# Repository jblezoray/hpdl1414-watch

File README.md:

# HPDL-1414 Watch

A minimalist watch built around an [HPDL-1414](https://www.datasheetarchive.com/HPDL-1414-datasheet.html) 4-character alphanumeric display, driven by an ATmega32 microcontroller.

If you're brave enougth, you'll find anything you need to build it yourself in this repo.

There is a demo of the watch on youtube:

## Hardware

| Component | Details                                 |
| --------- | --------------------------------------- |
| MCU       | atmega328p                              |
| Display   | HPDL-1414 (4 × 16-segment alphanumeric) |
| RTC       | DS3231 (I2C)                            |
| Storage   | EEPROM (SPI)                            |
| Input     | 2 buttons                               |

You'll also need:

- A 3D printer for the case,
- A provider for the HPDL1414 displays. Aliexpress is a good source.
- I ordered the pcbs from jlcpcb. I chose to solder everything myself, but I think it'd be more reasonnable to order with all the components already soldered, except the display as they don't list it.

## Features

- Time display with configurable transitions
- Adjustable luminosity (stored in EEPROM)
- Low-power screen-off state
- State machine architecture

## Project Structure

```
hpdl-1414.ino          # Main sketch
src/
  screen-hpdl1414/     # HPDL-1414 driver
  rtc-ds3231/          # DS3231 RTC driver
  button/              # Button handler
  blinker/             # LED blinker
  persist-configuration/ # EEPROM persistence
  vcc-controller/      # Power control
  states/              # State machine
  pins.h               # Pin definitions
3dmodels/              # Model for the 3D printed case
```

## Watch PCB schematics

Open the schematics (`pcb/hpdl1414/hpdl1414.kicad_sch` and `pcb/hpdl1414/hpdl1414.kicad_pcb`) with [kicad 9.0.1](https://www.kicad.org/).

Here is the first prototype of the PCB I made. It offers a full view of all the components on one side:

And here is the final one that is in the watch. It is much smaller:

## Watch case

Open ‘3dmodels/HPDL1414-watch-round.FCStd‘ with [FreeCAD 1.0.2](https://www.freecad.org/). Export it part by part, and print it with your favorite 3d printer. I have great results with a [Bambu lab A1 mini](https://bambulab.com/en-eu/a1-mini).

You'll have to use threaded inserts, and M1.5 screws to bolt the back of the case:

## Watch software

I used a Mac for developping this project, but it should work with little to no adjustement on linux. Sorry Windows users, you're on your own on this one.

Also, I find the Arduino IDE really bad, but their libs are ok. So only their CLI is needed. Once installed, everything can be handled by the Makefile.

### Prerequisites

- [Arduino CLI](https://arduino.github.io/arduino-cli/latest/installation/)
- An Arduino board used as ISP programmer (e.g. Uno)

```bash
# Install Arduino CLI (macOS)
$ brew install arduino-cli
$ arduino-cli core install arduino:avr
```

For reference:

```bash
$ arduino-cli version
arduino-cli  Version: 1.4.1 Commit: Homebrew Date: 2026-01-19T16:11:40Z
$ ${HOME}/Library/Arduino15/packages/arduino/tools/avrdude/8.0.0-arduino1/bin/avrdude -v
Avrdude version 8.0-arduino.1
```

### Setup

Copy `config.mk.example` to `config.mk` and fill in your values:

```makefile
ARDUINO_ROOT="/path/to/Arduino15/packages/arduino"  # e.g. ~/Library/Arduino15/packages/arduino
ARDUINO_CLI="/path/to/arduino-cli"
FQBN=arduino:avr:uno      # FQBN of the ISP programmer board
PORT=/dev/cu.usbmodem...  # port of the ISP programmer (make list-devices)
```

### Prepare an arduino to use as an ISP programmer

Plug the board to your computer and run:

```bash
# Flash the ISP programmer
make flash-isp-programmer
```

Now the board can be used as an ISP programmer.

### Plug the watch board to the ISP

IMPORTANT: Remove the battery from the watch board before pluging it!

Plug the ISP and the watch board:

- Arduino ground to GND on the watch board
- PIN 10 to RST
- PIN 11 to MOSI
- PIN 13 to CLK
- 5V to VCC
- PIN 12 to MISO

My working setup:

### Build & Flash

```bash
# First time: Set fuses on the target ATmega32
make set-target-clock-fuses

# Compile and upload the firmware
make upload
```

Run `make help` for all available targets.

## License

MIT

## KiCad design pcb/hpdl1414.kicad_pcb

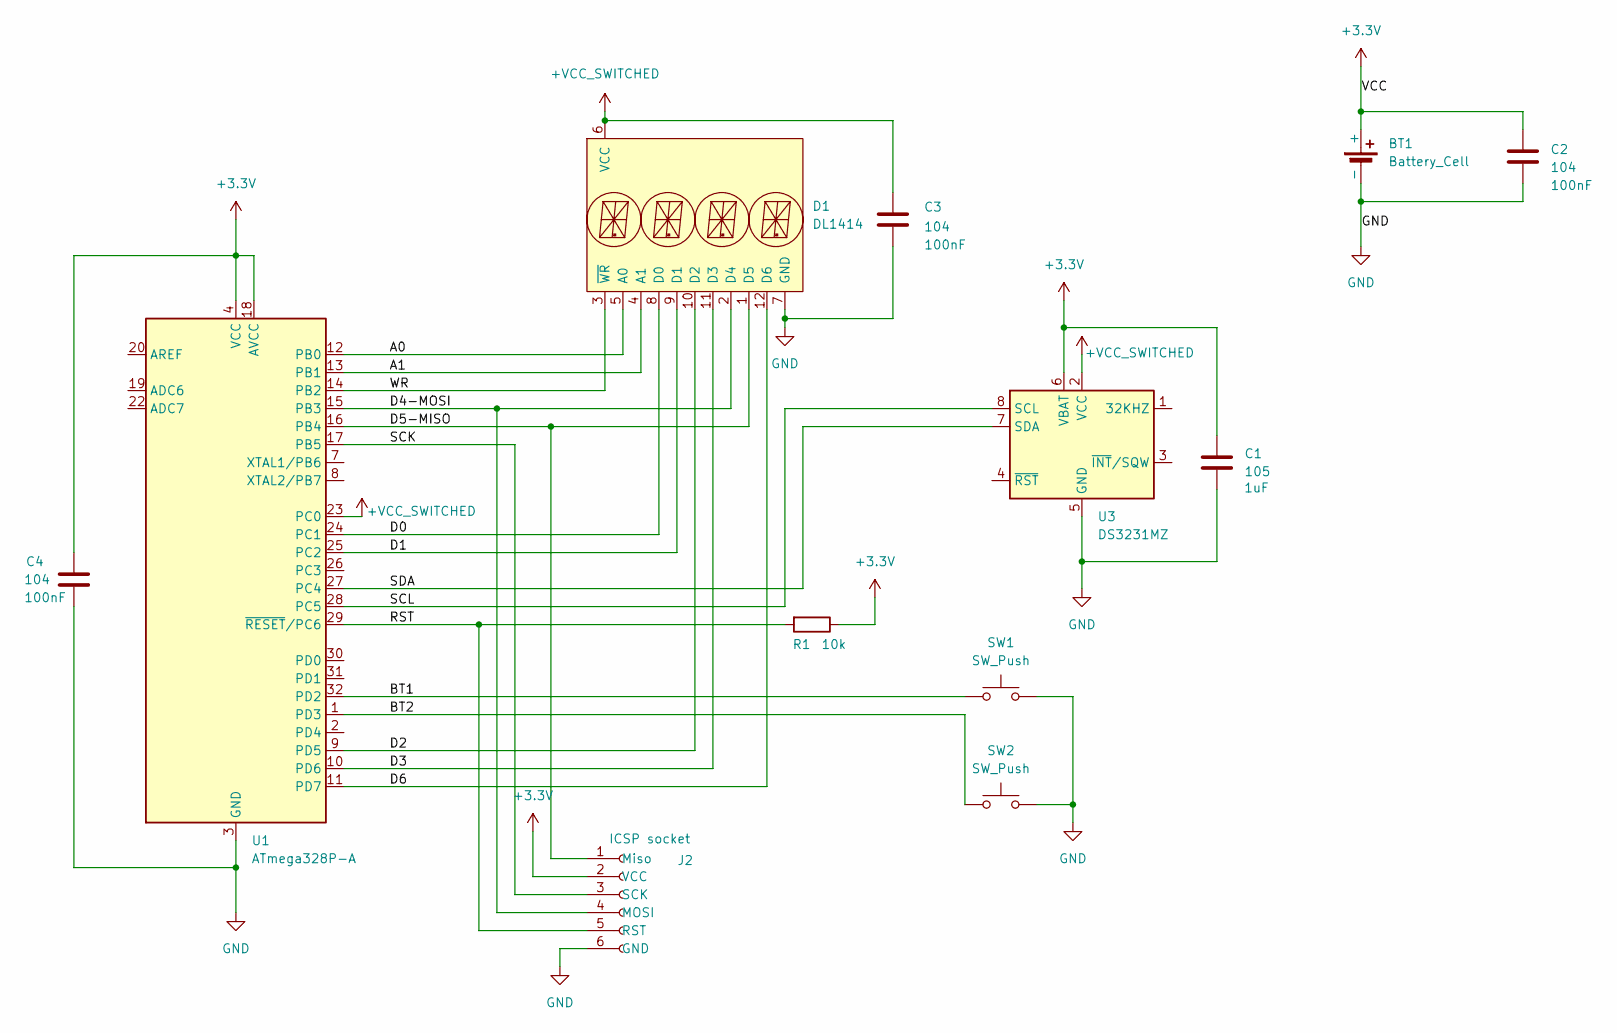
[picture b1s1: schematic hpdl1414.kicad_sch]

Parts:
BT1: Battery_Cell; BatteryHolder_Multicomp_BC-2001_1x2032
C1: 105; C_0805_2012Metric_Pad1.18x1.45mm_HandSolder
C2, C3, C4: 104; C_0805_2012Metric_Pad1.18x1.45mm_HandSolder
D1: DL1414
J2: ICSP socket; JST_GH_BM06B-GHS-TBT_1x06-1MP_P1.25mm_Vertical
R1: 10k; R_0805_2012Metric_Pad1.20x1.40mm_HandSolder
SW1, SW2: SW_Push; Panasonic_EVQPUJ_EVQPUA
U1: ATmega328P-A; TQFP-32_7x7mm_P0.8mm
U3: DS3231MZ; SOIC-8_3.9x4.9mm_P1.27mm

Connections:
+3.3V: BT1.1 (+), C1.1, C2.1, C4.1, J2.2 (VCC), R1.1, U1.4 (VCC), U1.6 (VCC), U1.18 (AVCC), U3.6 (VBAT)
+VCC_SWITCHED: C3.1, D1.6 (VCC), U1.23 (PC0), U3.2 (VCC)
/A0: D1.5 (A0), U1.12 (PB0)
/A1: D1.4 (A1), U1.13 (PB1)
/BT1: SW1.1, U1.32 (PD2)
/BT2: SW2.1, U1.1 (PD3)
/D0: D1.8 (D0), U1.24 (PC1)
/D1: D1.9 (D1), U1.25 (PC2)
/D2: D1.10 (D2), U1.9 (PD5)
/D3: D1.11 (D3), U1.10 (PD6)
/D4-MOSI: D1.2 (D4), J2.4 (MOSI), U1.15 (PB3)
/D5-MISO: D1.1 (D5), J2.1 (Miso), U1.16 (PB4)
/D6: D1.12 (D6), U1.11 (PD7)
/RST: J2.5 (RST), R1.2, U1.29 (~RESET/PC6)
/SCK: J2.3 (SCK), U1.17 (PB5)
/SCL: U1.28 (PC5), U3.8 (SCL)
/SDA: U1.27 (PC4), U3.7 (SDA)
/WR: D1.3 (~WR), U1.14 (PB2)
GND: BT1.2 (-), C1.2, C2.2, C3.2, C4.2, D1.7 (GND), J2.6 (GND), SW1.2, SW2.2, U1.3 (GND), U1.5 (GND), U1.21 (GND), U3.5 (GND)

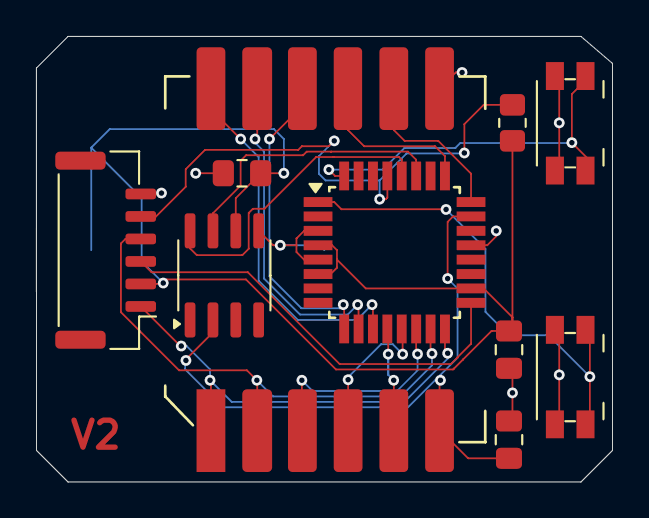
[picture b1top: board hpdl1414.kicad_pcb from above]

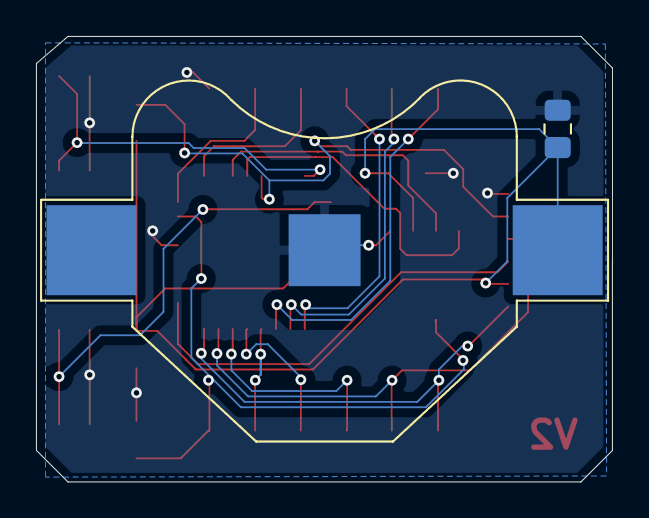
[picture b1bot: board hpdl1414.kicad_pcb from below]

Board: 2 copper layers, 32.0 x 24.8 mm, 12 parts (2 on the bottom side), 19 nets.

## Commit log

2026-04-14 source code
2026-04-14 Readme
2026-04-14 3d models
2026-04-14 fix bap chip ref in readme
2026-04-14 demo video
2026-05-05 isp setup guide
